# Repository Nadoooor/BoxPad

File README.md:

# BoxPad
---------------------

-------------------

## Description:
A macropad in a cheese box. This is a macropad made from scratch with MX switches, and it can be totaly made by DIYing (Recycling, and handwiring), or by just printing the case and the PCB.

## Why making this?
Well, I have many hardware components and I want to make something with them, but 3D printing and PCB printing in Egypt costs so much, so gonna DIY it from scratch.

> [!NOTE]
> AI helped a lil with the firmware DOCS because KMK & QMK are kinda outdated

## Features:
- MX switchs in a 2x4 Metrix.
- OLED 0.96' Screen.
- Rotary Encoder.
- NEO sticks.

## Photos & Demo:

### Schematic:

### PCB:

### 3D PCB:

### 3D Assembly:

> [!NOTE]
> Here you are the [Fusion Assembly](https://a360.co/4h1u5xi)

### Demo Video:
You will find this video [Here](https://youtube.com/shorts/f90f9HWrAXo?feature=share)

## How to Build (Using Printed Parts):

1. Print all your parts.
2. Put the MX Switches in their places on the cover.
3. Solder the screen and the Rotary Encoder.
4. Place the PCB under the switches and Solder them.
5. Solder the XIAO on the board, using its pin header so you can control its height.
6. Solder the JST connector of the NEOsticks 
7. Connect the NEOsticks, and put them inside the case corners using hot glue.
8. Download CircuitPython, and install it into the XIAO RP2040.
9. Copy What's inside the [Firmware Folder](Firmware), and paste it inside the CIRCUITPY Drive.
10. Replug the MCU and it will run automaticly.

## How to Build (DIYing):

1. Find any Box to recycle. (Like a cheese box).
2. Cut the exact mesurements of the SWs, rotary encoder, and OLED screen holes on the cover of the box.
3. Put the SWs, and the rotary encoder on the cover of the box.
4. Hand wire and solder the Diodes and the ROWs and COLs from the back, also the Rotary encoder and the OLED.
5. Solder a 4 NEOsticks chain, and using hot glue put them inside the box.
6. Connect everything to the XIAO PinHeader (or use a small breadboard).
7. Connect the XIAO to the PC/Laptop.
8. Use the same steps as in step (8) in (How to bulid using printed parts.)

---------------
# Made with ❤️, By @Nadoooor

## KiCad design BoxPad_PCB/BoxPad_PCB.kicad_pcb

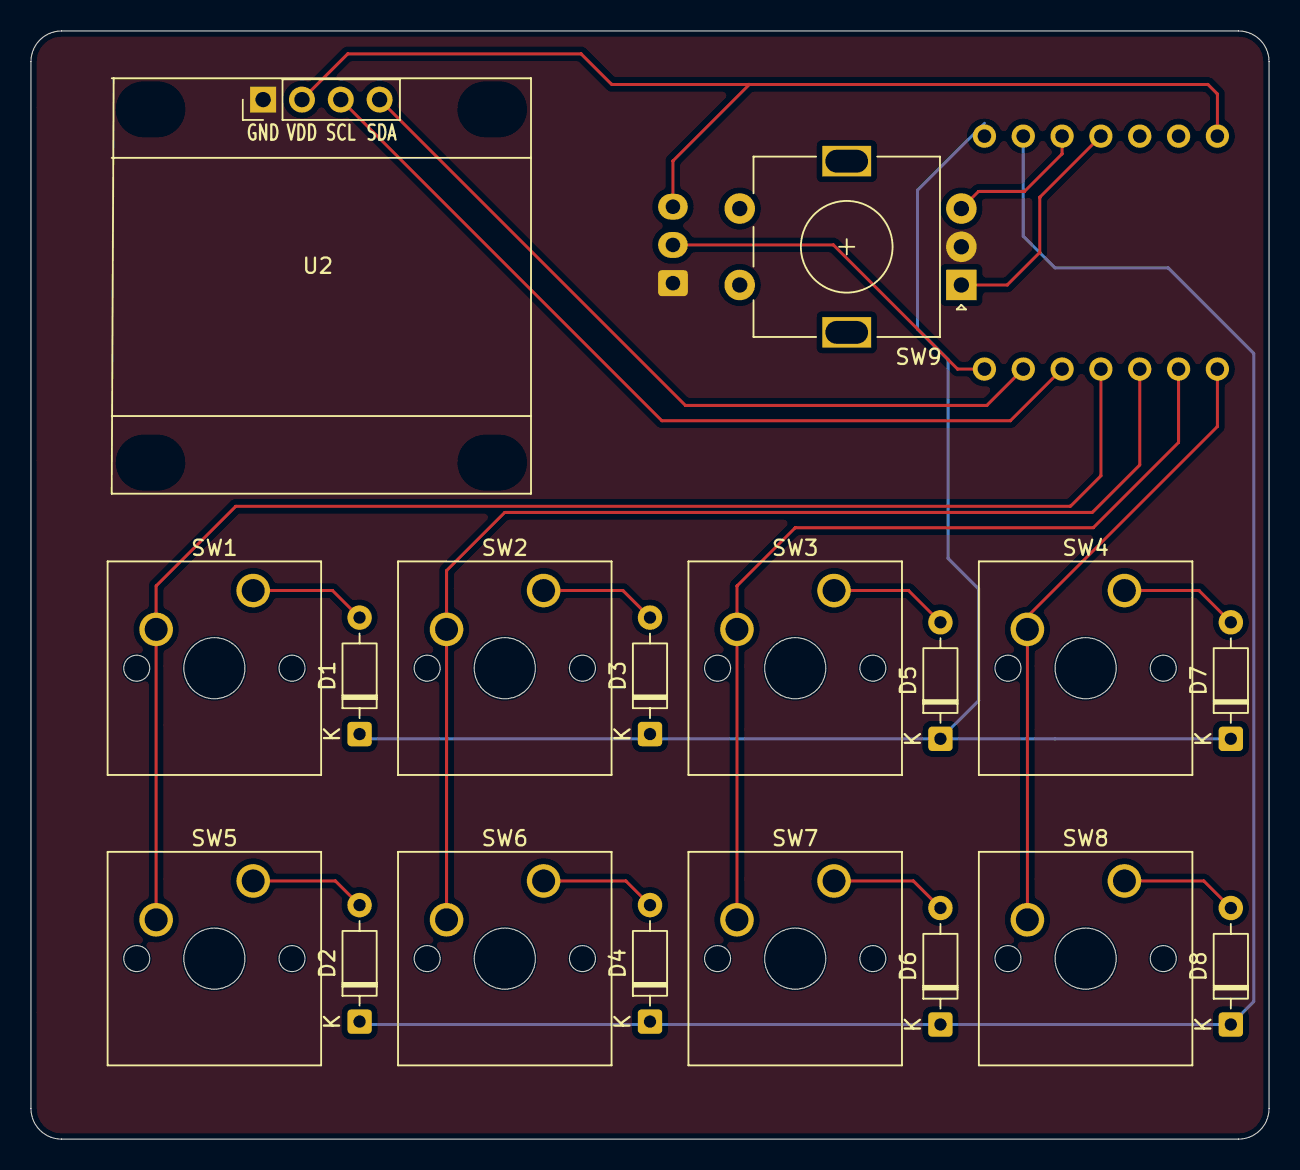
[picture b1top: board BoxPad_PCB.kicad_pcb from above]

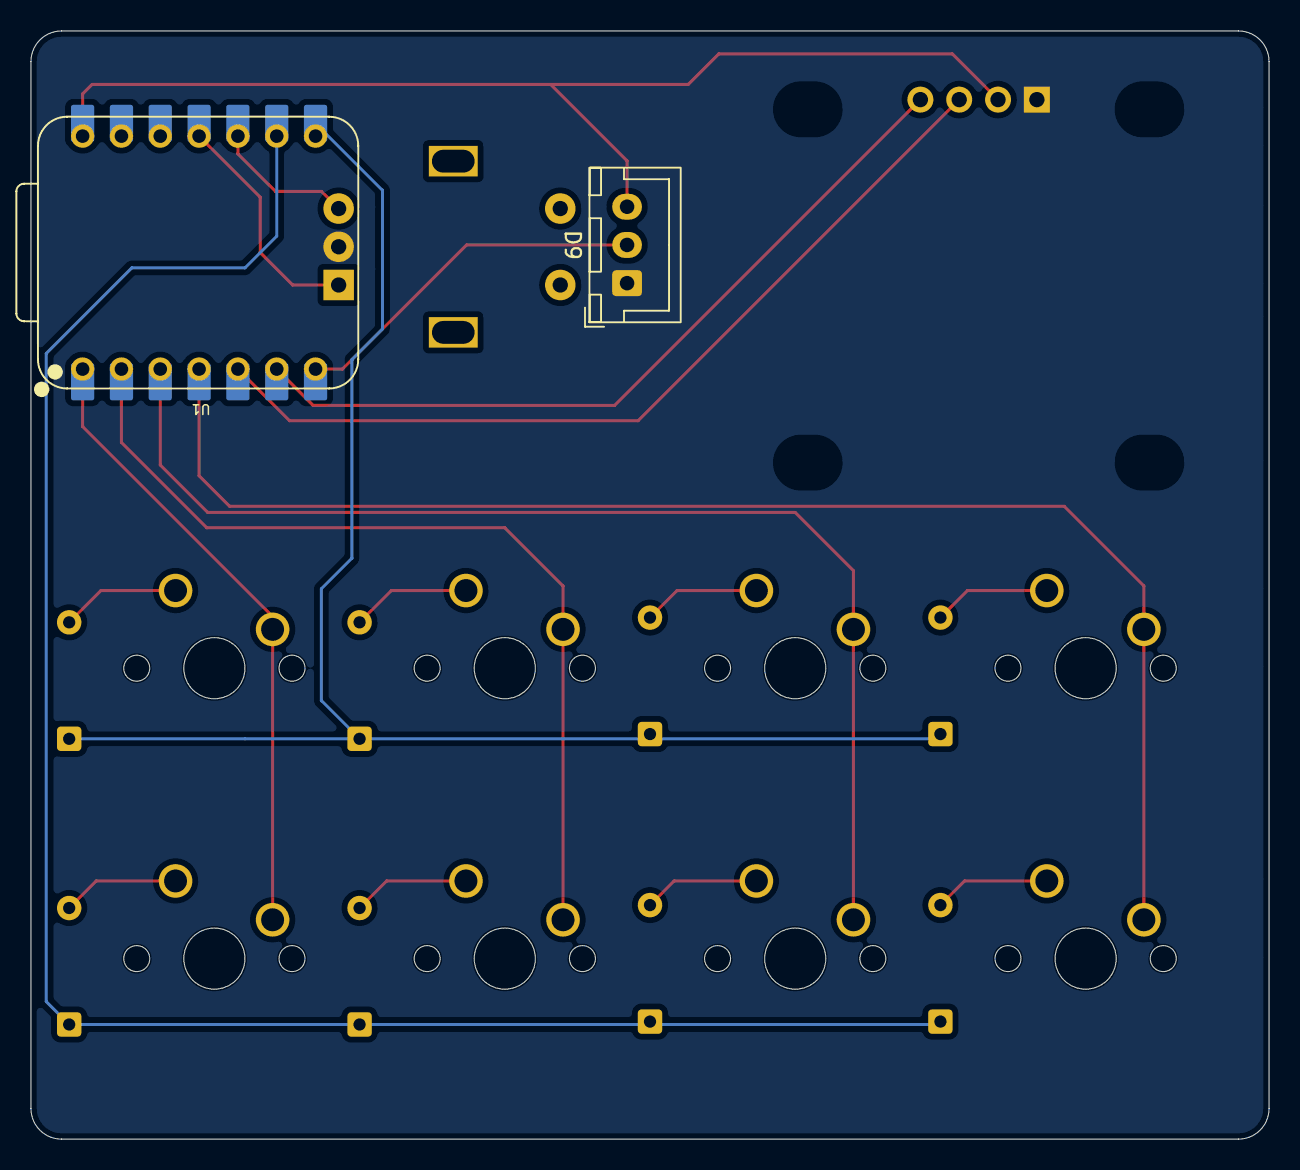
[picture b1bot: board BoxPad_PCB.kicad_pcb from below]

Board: 2 copper layers, 81.0 x 72.5 mm, 20 parts (2 on the bottom side), 21 nets.

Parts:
D1, D2, D3, D4, D5, D6, D7, D8: D; D_DO-35_SOD27_P7.62mm_Horizontal
D9: WS2812; JST_XH_B3B-XH-A_1x03_P2.50mm_Vertical
SW1, SW2, SW3, SW4, SW5, SW6, SW7, SW8: SW_Push_45deg; SW_Cherry_MX_1.00u_PCB_Wtih_3D
SW9: RotaryEncoder_Switch; RotaryEncoder_Alps_EC11E-Switch_Vertical_H20mm
U1: XIAO-RP2040-SMD; XIAO-RP2040-DIP
U2: OLED_I2C; Display_128x64_096_I2C

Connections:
+5V: D9.3 (VCC), U1.14 (VBUS), U2.2 (VCC)
A_Encoder: SW9.A, U1.11 (D10)
B_Encoder: SW9.B, U1.10 (D9)
COL1: SW1.2, SW5.2, U1.4 (D3)
COL2: SW2.2, SW6.2, U1.3 (D2)
COL3: SW3.2, SW7.2, U1.2 (D1)
COL4: SW4.2, SW8.2, U1.1 (D0)
GND: D9.1 (VSS), SW9.C, U2.1 (GND)
NEO: D9.2 (DIN), U1.7 (D6)
unnamed: D1.2 (A), SW1.1
unnamed: D2.2 (A), SW5.1
unnamed: D3.2 (A), SW2.1
unnamed: D4.2 (A), SW6.1
unnamed: D5.2 (A), SW3.1
unnamed: D6.2 (A), SW7.1
unnamed: D7.2 (A), SW4.1
unnamed: D8.2 (A), SW8.1
ROW1: D1.1 (K), D3.1 (K), D5.1 (K), D7.1 (K), U1.8 (D7)
ROW2: D2.1 (K), D4.1 (K), D6.1 (K), D8.1 (K), U1.9 (D8)
SCL_OLED: U1.5 (D4), U2.3 (SCL)
SDA_OLED: U1.6 (D5), U2.4 (SDA)

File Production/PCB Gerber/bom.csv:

Designator,Footprint,Quantity,Value,LCSC Part #
"D1, D2, D3, D4, D5, D6, D7, D8",D_DO-35_SOD27_P7.62mm_Horizontal,8,D,
D9,JST_XH_B3B-XH-A_1x03_P2.50mm_Vertical,1,WS2812,
"SW1, SW2, SW3, SW4, SW5, SW6, SW7, SW8",SW_Cherry_MX_1.00u_PCB_Wtih_3D,8,SW_Push_45deg,
SW9,RotaryEncoder_Alps_EC11E-Switch_Vertical_H20mm,1,RotaryEncoder_Switch,
U1,XIAO-RP2040-DIP,1,XIAO-RP2040-SMD,
U2,Display_128x64_096_I2C,1,OLED_I2C,
